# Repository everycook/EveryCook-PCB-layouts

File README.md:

EveryCook-PCB-layouts
=====================

All PCB layouts for the latest EveryCook. They work together, therefore they have a common repository

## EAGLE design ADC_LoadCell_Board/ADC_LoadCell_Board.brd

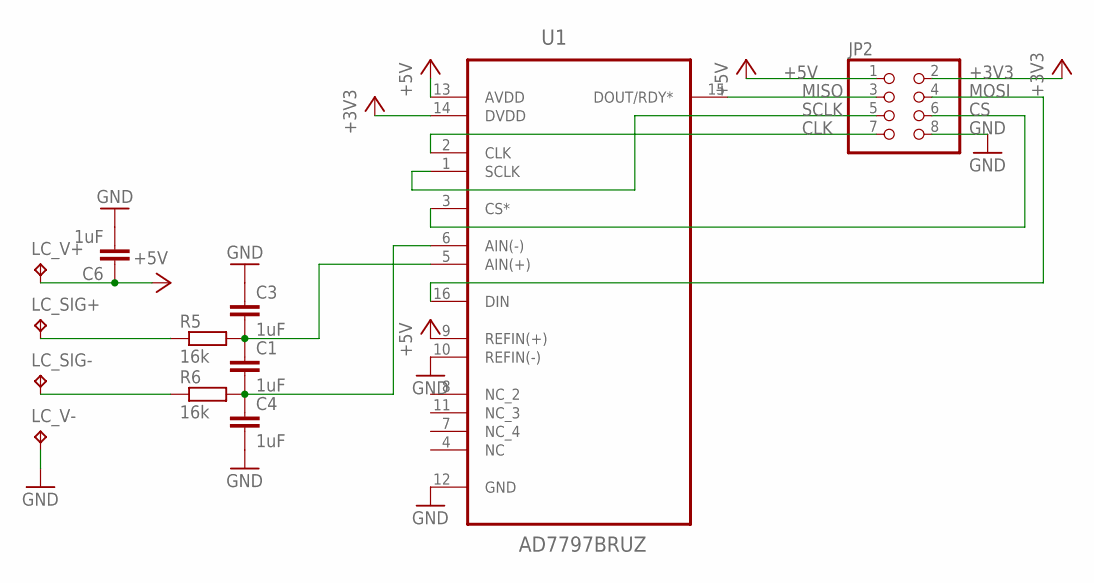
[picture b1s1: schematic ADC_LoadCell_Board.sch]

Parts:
C1, C3, C4, C6: 1uF; C0805
JP2: PINHD-2X4; 2X04
LC_SIG+: TPB1,27; B1,27
LC_SIG-: TPB1,27; B1,27
LC_V+: TPB1,27; B1,27
LC_V-: TPB1,27; B1,27
R5, R6: 16k; R0805
U1: AD7797BRUZ; SOP65P640X120-16N

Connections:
+3V3: JP2.2, U1.14 (DVDD)
+5V: C6.1, JP2.1, LC_V+.TP, U1.9 (REFIN(+)), U1.13 (AVDD)
CLK: JP2.7, U1.2 (CLK)
CS: JP2.6, U1.3 (CS*)
GND: C3.1, C4.2, C6.2, JP2.8, LC_V-.TP, U1.10 (REFIN(-)), U1.12 (GND)
MISO: JP2.3, U1.15 (DOUT/RDY*)
MOSI: JP2.4, U1.16 (DIN)
unnamed: LC_SIG+.TP, R5.1
unnamed: LC_SIG-.TP, R6.1
unnamed: C1.1, C3.2, R5.2, U1.5 (AIN(+))
unnamed: C1.2, C4.1, R6.2, U1.6 (AIN(-))
SCLK: JP2.5, U1.1 (SCLK)

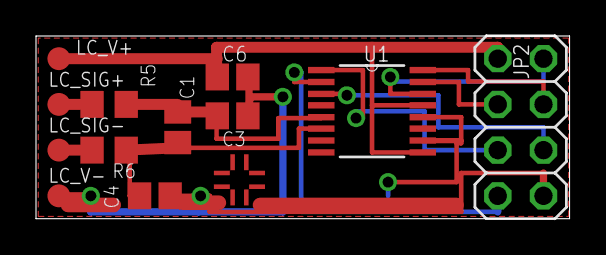
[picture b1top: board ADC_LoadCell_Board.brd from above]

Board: 2 copper layers, 29.6 x 10.2 mm, 13 parts (0 on the bottom side), 12 nets.

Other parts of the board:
U$2: PASSER

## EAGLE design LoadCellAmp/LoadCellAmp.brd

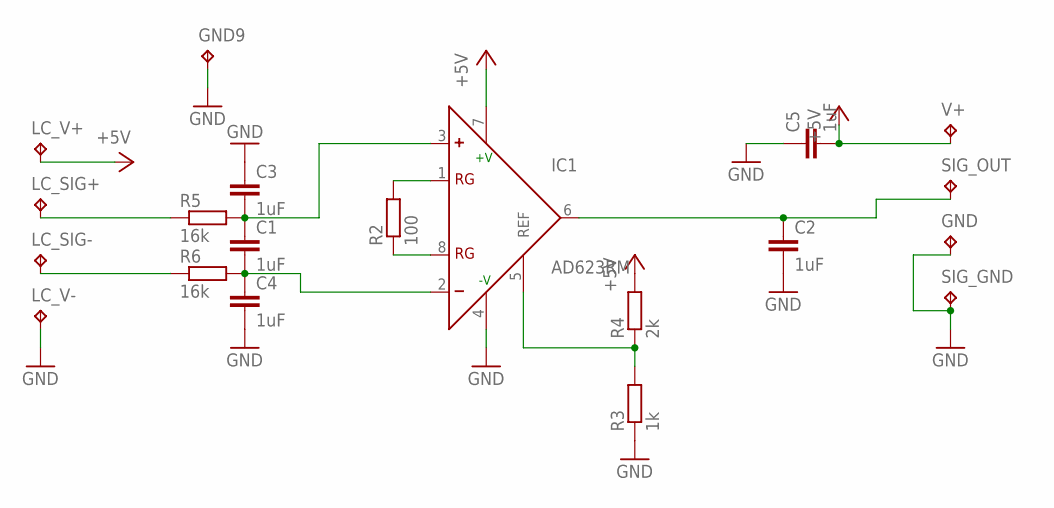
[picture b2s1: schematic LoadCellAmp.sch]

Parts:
C1, C2, C3, C4, C5: 1uF; C0805
GND, GND9: TPB1,27; B1,27
IC1: AD623RM; MSOP08
LC_SIG+: TPB1,27; B1,27
LC_SIG-: TPB1,27; B1,27
LC_V+: TPB1,27; B1,27
LC_V-: TPB1,27; B1,27
R2: 100; R0805
R3: 1k; R0805
R4: 2k; R0805
R5, R6: 16k; R0805
SIG_GND: TPB1,27; B1,27
SIG_OUT: TPB1,27; B1,27
V+: TPB1,27; B1,27

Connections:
+5V: C5.2, IC1.7 (+V), LC_V+.TP, R4.2, V+.TP
GND: C2.2, C3.1, C4.2, C5.1, GND.TP, GND9.TP, IC1.4 (-V), LC_V-.TP, R3.1, SIG_GND.TP
unnamed: IC1.1 (RG), R2.2
unnamed: IC1.8 (RG), R2.1
unnamed: IC1.5 (REF), R3.2, R4.1
unnamed: C2.1, IC1.6 (OUT), SIG_OUT.TP
unnamed: LC_SIG+.TP, R5.1
unnamed: LC_SIG-.TP, R6.1
unnamed: C1.1, C3.2, IC1.3 (+), R5.2
unnamed: C1.2, C4.1, IC1.2 (-), R6.2

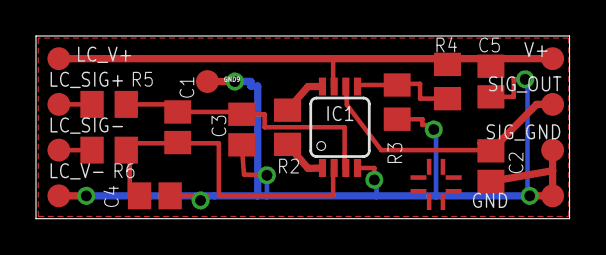
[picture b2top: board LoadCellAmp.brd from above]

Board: 2 copper layers, 29.6 x 10.2 mm, 21 parts (0 on the bottom side), 10 nets.

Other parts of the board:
U$2: PASSER

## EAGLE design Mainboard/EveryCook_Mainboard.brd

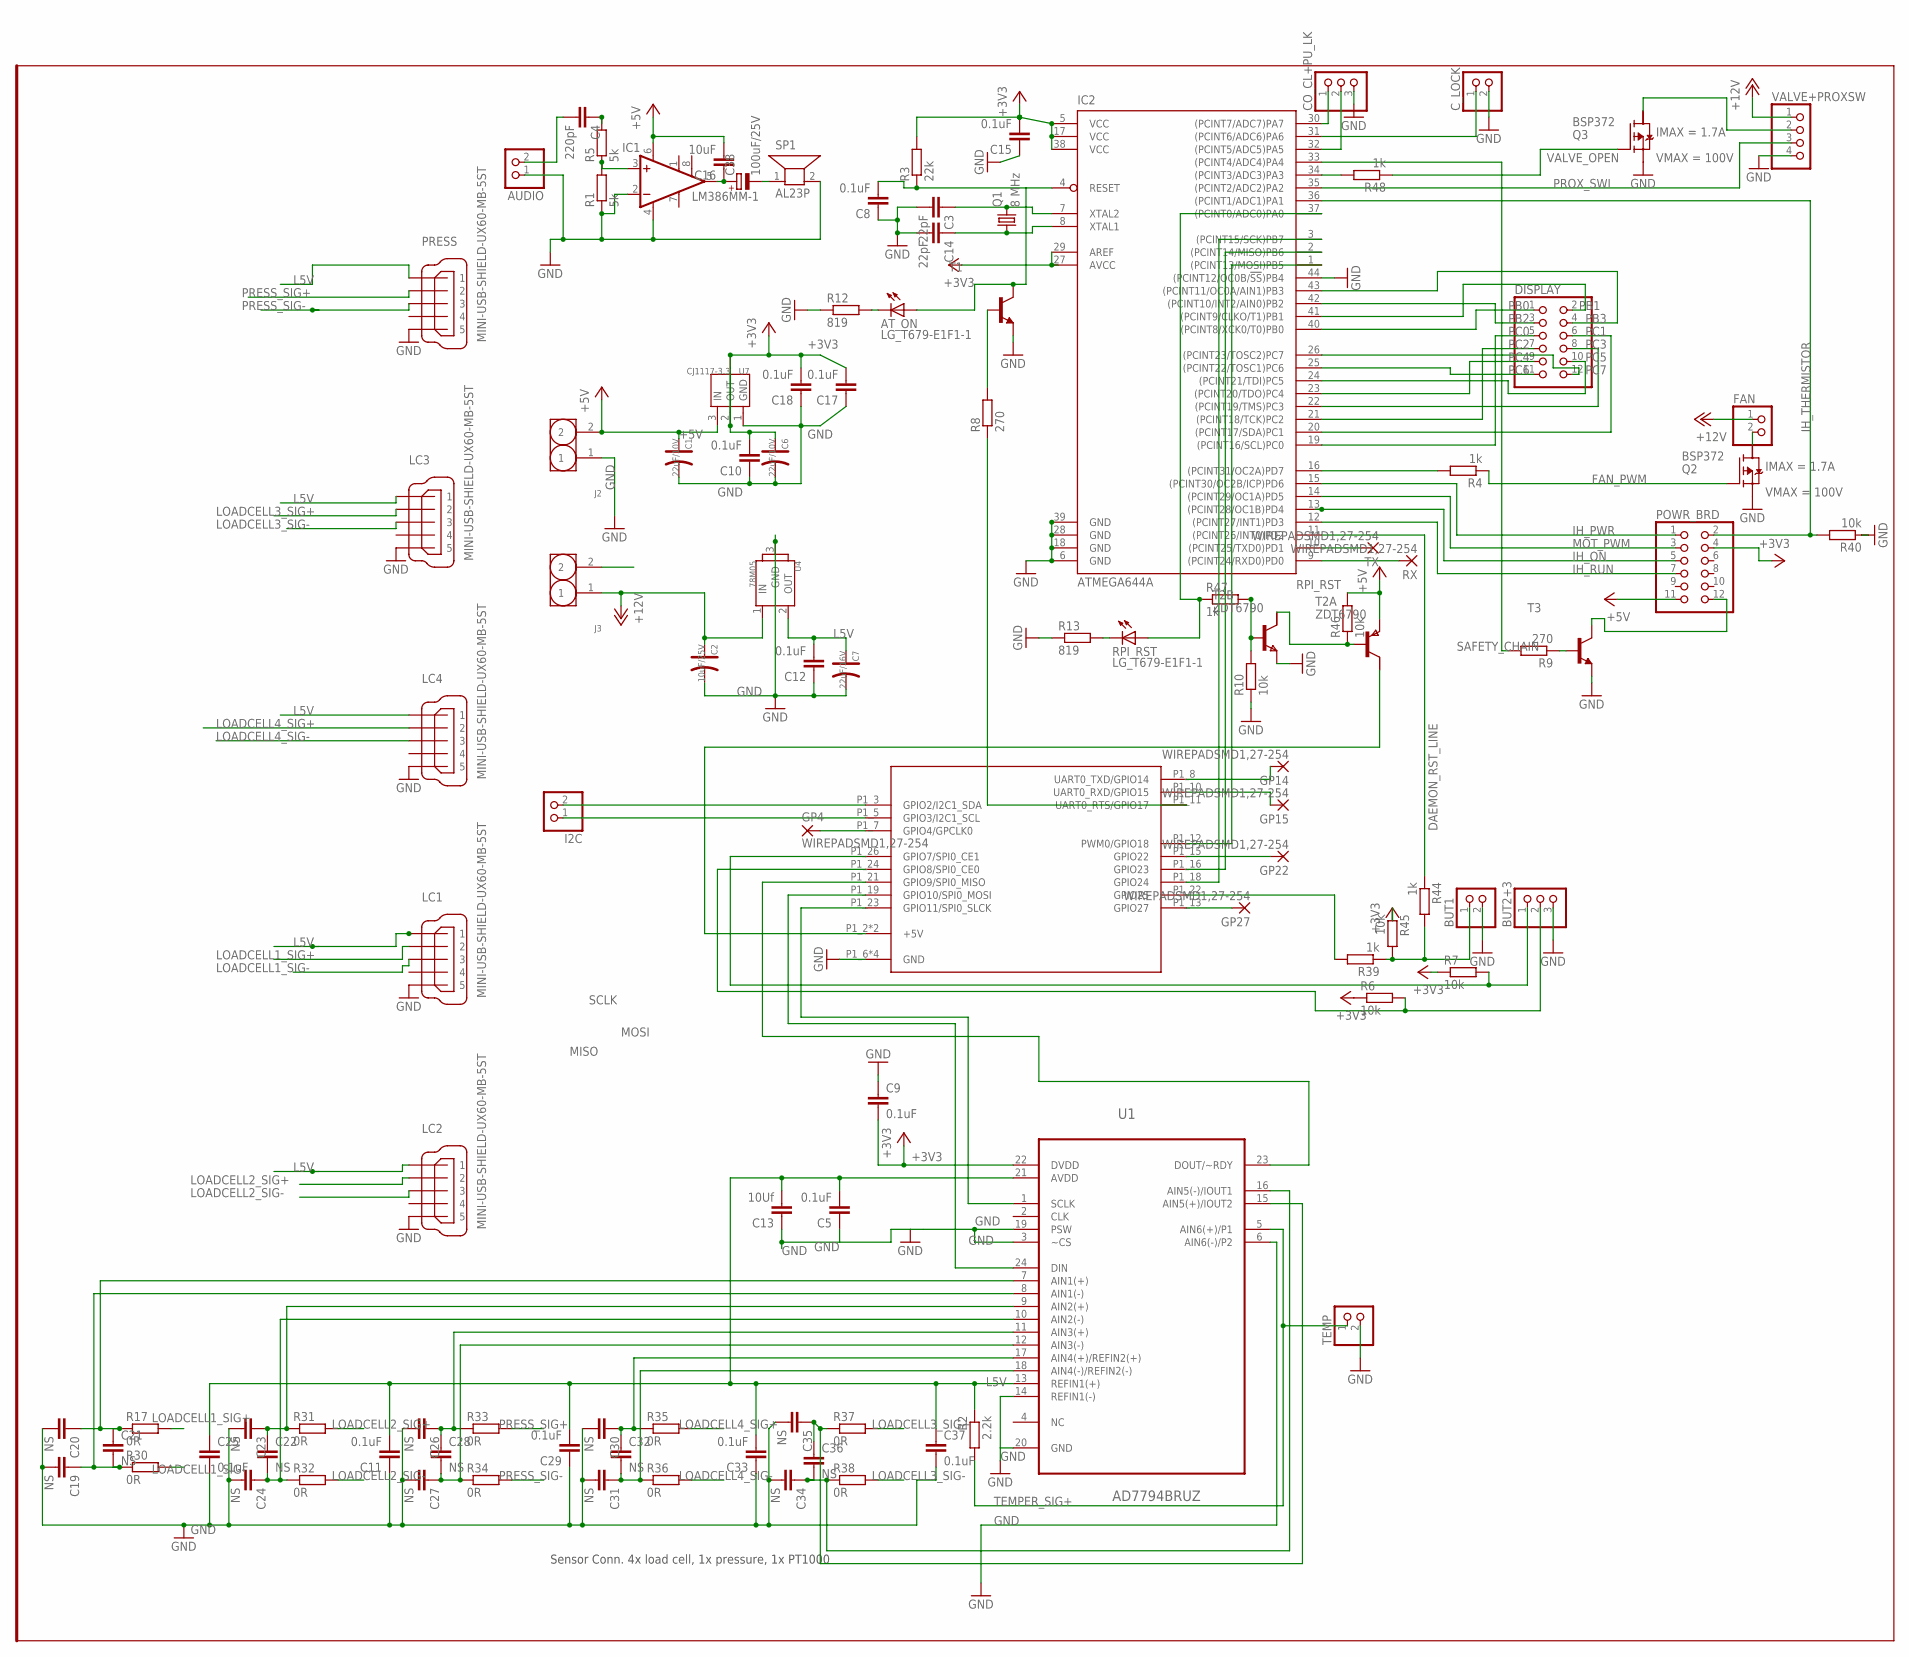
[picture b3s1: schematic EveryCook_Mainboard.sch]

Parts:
AT_ON: LG_T679-E1F1-1; PLCC2
AUDIO: PINHD-1X2; 1X02
BUT1: PINHD-1X2; 1X02
BUT2+3: PINHD-1X3; 1X03
C1, C6: 22uF/10V; AVX-A
C2: 10uF/25V; ELECTRO-SMD-B-4.8MM
C3, C14: 22pF; C0805
C4: 220pF; C0805
C5, C8, C9, C10, C11, C12, C15, C17, C18, C25, C29, C33, C37: 0.1uF; C0805
C7: 22uF/16V; ELECTRO-SMD-B-4.8MM
C13: 10Uf; C0805
C16: 10uF; C0805
C19, C20, C21, C22, C23, C24, C26, C27, C28, C30, C31, C32, C34, C35, C36: NS; C0805
C38: 100uF/25V; UD-6,3X7,7_NICHICON
CO_CL+PU_LK: PINHD-1X3; 1X03
C_LOCK: PINHD-1X2; 1X02
DISPLAY: PINHD-2X6; 2X06
FAN: PINHD-1X2; 1X02
GP4, GP14, GP15, GP22, GP27: WIREPADSMD1,27-254; SMD1,27-2,54
I2C: PINHD-1X2; 1X02
IC1: LM386MM-1; MMSOP08
IC2: ATMEGA644A; TQFP44
J2, J3: HEADER-2P-5.0; 2P-5.0
LC1, LC2, LC3, LC4: MINI-USB-SHIELD-UX60-MB-5ST; UX60-MB-5ST
POWR_BRD: PINHD-2X6; 2X06
PRESS: MINI-USB-SHIELD-UX60-MB-5ST; UX60-MB-5ST
Q1: 8 MHz; HC49UP
Q2, Q3: BSP372; PG-SOT-223
R1, R5: 5k; R0805
R2: 2.2k; R0805
R3: 22k; R0805
R4, R39, R44, R47, R48: 1k; R0805
R6, R7, R10, R40, R45, R46: 10k; R0805
R8, R9: 270; R0805
R12, R13: 819; R0805
R17, R30, R31, R32, R33, R34, R35, R36, R37, R38: 0R; R0805
RPI_RST: LG_T679-E1F1-1; PLCC2
RX: WIREPADSMD1,27-254; SMD1,27-2,54
SP1: AL23P
T1, T3: MMBT2222ALT1-NPN-SOT23-BEC; SOT23-BEC
T2: ZDT6790; SM8
TEMP: PINHD-1X2; 1X02
TX: WIREPADSMD1,27-254; SMD1,27-2,54
U1: AD7794BRUZ; SOP65P640X120-24N
U4: 78M05; TO252
U7: CJ1117-3.3; SOT89
U$5: RPI-B-V2
VALVE+PROXSW: PINHD-1X4; 1X04

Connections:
+3V3: C6.+, C9.2, C10.2, C15.2, C17.2, C18.2, IC2.5 (VCC), IC2.17 (VCC), IC2.27 (AVCC), IC2.29 (AREF), IC2.38 (VCC), POWR_BRD.4, R3.2, R6.1, R7.1, R45.1, U1.22 (DVDD), U7.2 (OUT), U7.4 (TAB)
+5V: C1.+, C16.2, IC1.6 (VS), J2.2, POWR_BRD.11, R46.2, T2.1 (E), U7.3 (IN)
+12V: C2.+, FAN.1, J3.1, U4.1 (IN), VALVE+PROXSW.1
ATMEL_RST: AT_ON.A, C8.2, IC2.4 (RESET), R3.1, T1.C
AT_MISO: IC2.2 ((PCINT14/MISO)PB6), U$5.P1_16 (GPIO23)
AT_MOSI: IC2.1 ((PCINT13/MOSI)PB5), U$5.P1_12 (PWM0/GPIO18)
C_CLOSE: CO_CL+PU_LK.1, IC2.30 ((PCINT7/ADC7)PA7)
DAEMON_RST_LINE: IC2.11 ((PCINT26/INT0)PD2), R44.1
FAN_PWM: Q2.1 (G), R4.1
GND: AUDIO.1, BUT1.2, BUT2+3.3, C1.-, C2.-, C3.2, C5.1, C6.-, C7.-, C8.1, C9.1, C10.1, C11.1, C12.1, C13.1, C14.2, C15.1, C17.1, C18.1, C19.2, C20.2, C23.2, C24.2, C25.2, C26.2, C27.2, C29.1, C30.2, C31.2, C33.1, C34.2, C35.2, C37.2, CO_CL+PU_LK.3, C_LOCK.2, IC1.2 (-IN), IC1.4 (GND), IC2.6 (GND), IC2.18 (GND), IC2.28 (GND), IC2.39 (GND), IC2.44 ((PCINT12/OC0B/!SS!)PB4), J2.1, LC1.5, LC2.5, LC3.5, LC4.5, PRESS.5, Q2.3 (S), Q3.3 (S), R1.1, R10.1, R12.1, R13.1, R40.1, SP1.2, T1.E, T2.3 (E), T3.E, TEMP.2, U1.3 (~CS), U1.6 (AIN6(-)/P2), U1.14 (REFIN1(-)), U1.19 (PSW), U1.20 (GND), U4.3 (GND), U7.1 (GND), U$5.P1_6 (GND), U$5.P1_14 (GND), U$5.P1_20 (GND), U$5.P1_25 (GND), VALVE+PROXSW.4
IH_ON: IC2.13 ((PCINT28/OC1B)PD4), POWR_BRD.5
IH_PWR: IC2.15 ((PCINT30/OC2B/ICP)PD6), POWR_BRD.1
IH_RUN: IC2.12 ((PCINT27/INT1)PD3), POWR_BRD.7
IH_THERMISTOR: IC2.36 ((PCINT1/ADC1)PA1), POWR_BRD.2, R40.2
L5V: C5.2, C7.+, C11.2, C12.2, C13.2, C25.1, C29.2, C33.2, C37.1, LC1.1, LC2.1, LC3.1, LC4.1, PRESS.1, R2.1, U1.13 (REFIN1(+)), U1.21 (AVDD), U4.2 (OUT)
LOADCELL1_SIG+: LC1.2, R17.2
LOADCELL1_SIG-: LC1.3, R30.2
LOADCELL2_SIG+: LC2.2, R31.2
LOADCELL2_SIG-: LC2.3, R32.2
LOADCELL3_SIG+: LC3.2, R37.2
LOADCELL3_SIG-: LC3.3, R38.2
LOADCELL4_SIG+: LC4.2, R35.2
LOADCELL4_SIG-: LC4.3, R36.2
MISO: U1.23 (DOUT/~RDY), U$5.P1_21 (GPIO9/SPI0_MISO)
MOSI: U1.24 (DIN), U$5.P1_19 (GPIO10/SPI0_MOSI)
MOT_PWM: IC2.14 ((PCINT29/OC1A)PD5), POWR_BRD.3
unnamed: I2C.1, U$5.P1_5 (GPIO3/I2C1_SCL)
unnamed: C3.1, IC2.7 (XTAL2), Q1.2
unnamed: C4.1, R5.2
unnamed: C34.1, C36.2, R38.1, U1.16 (AIN5(-)/IOUT1)
unnamed: I2C.2, U$5.P1_3 (GPIO2/I2C1_SDA)
unnamed: C14.1, IC2.8 (XTAL1), Q1.1
unnamed: POWR_BRD.12, T3.C
unnamed: C20.1, C21.1, R17.1, U1.7 (AIN1(+))
unnamed: IC2.16 ((PCINT31/OC2A)PD7), R4.2
unnamed: R9.1, T3.B
unnamed: IC2.10 ((PCINT25/TXD0)PD1), TX.1
unnamed: IC1.3 (+IN), R1.2, R5.1
unnamed: IC2.9 ((PCINT24/RXD0)PD0), RX.1
unnamed: GP4.1, U$5.P1_7 (GPIO4/GPCLK0)
unnamed: GP27.1, U$5.P1_13 (GPIO27)
unnamed: GP22.1, U$5.P1_15 (GPIO22)
unnamed: GP15.1, U$5.P1_10 (UART0_RXD/GPIO15)
unnamed: GP14.1, U$5.P1_8 (UART0_TXD/GPIO14)
unnamed: C16.1, C38.+, IC1.5 (OUT)
unnamed: C38.-, SP1.1
unnamed: C22.1, C23.1, R31.1, U1.9 (AIN2(+))
unnamed: R8.2, T1.B
unnamed: AUDIO.2, C4.2
unnamed: AT_ON.C, R12.2
unnamed: R13.2, RPI_RST.C
unnamed: C22.2, C24.1, R32.1, U1.10 (AIN2(-))
unnamed: C27.1, C28.2, R34.1, U1.12 (AIN3(-))
unnamed: C30.1, C32.1, R35.1, U1.17 (AIN4(+)/REFIN2(+))
unnamed: C31.1, C32.2, R36.1, U1.18 (AIN4(-)/REFIN2(-))
unnamed: C35.1, C36.1, R37.1, U1.15 (AIN5(+)/IOUT2)
unnamed: C19.1, C21.2, R30.1, U1.8 (AIN1(-))
unnamed: FAN.2, Q2.2 (D)
unnamed: C26.1, C28.1, R33.1, U1.11 (AIN3(+))
unnamed: T2.8 (C1), U$5.P1_2 (+5V), U$5.P1_4 (+5V)
unnamed: C_LOCK.1, IC2.31 ((PCINT6/ADC6)PA6)
unnamed: BUT2+3.1, R7.2, U$5.P1_26 (GPIO7/SPI0_CE1)
unnamed: BUT2+3.2, R6.2, U$5.P1_24 (GPIO8/SPI0_CE0)
unnamed: R39.2, U$5.P1_22 (GPIO25)
unnamed: IC2.34 ((PCINT3/ADC3)PA3), R48.2
unnamed: BUT1.1, R39.1, R44.2, R45.2
unnamed: R10.2, R47.2, T2.4 (B)
unnamed: R46.1, T2.2 (B), T2.5 (C1)
unnamed: Q3.2 (D), VALVE+PROXSW.2
PB0: DISPLAY.1, IC2.40 ((PCINT8/XCK0/T0)PB0)
PB1: DISPLAY.2, IC2.41 ((PCINT9/CLKO/T1)PB1)
PB2: DISPLAY.3, IC2.42 ((PCINT10/INT2/AIN0)PB2)
PB3: DISPLAY.4, IC2.43 ((PCINT11/OC0A/AIN1)PB3)
PC0: DISPLAY.5, IC2.19 ((PCINT16/SCL)PC0)
PC1: DISPLAY.6, IC2.20 ((PCINT17/SDA)PC1)
PC2: DISPLAY.7, IC2.21 ((PCINT18/TCK)PC2)
PC3: DISPLAY.8, IC2.22 ((PCINT19/TMS)PC3)
PC4: DISPLAY.9, IC2.23 ((PCINT20/TDO)PC4)
PC5: DISPLAY.10, IC2.24 ((PCINT21/TDI)PC5)
PC6: DISPLAY.11, IC2.25 ((PCINT22/TOSC1)PC6)
PC7: DISPLAY.12, IC2.26 ((PCINT23/TOSC2)PC7)
PGND: J3.2
PRESS_SIG+: PRESS.2, R33.2
PRESS_SIG-: PRESS.3, R34.2
PROX_SWI: IC2.35 ((PCINT2/ADC2)PA2), VALVE+PROXSW.3
P_LOCK: CO_CL+PU_LK.2, IC2.32 ((PCINT5/ADC5)PA5)
RPI_ATMEL_RST: R8.1, U$5.P1_11 (UART0_RTS/GPIO17)
RPI_RST: IC2.37 ((PCINT0/ADC0)PA0), R47.1, RPI_RST.A
SAFETY_CHAIN: IC2.33 ((PCINT4/ADC4)PA4), R9.2
SCK: IC2.3 ((PCINT15/SCK)PB7), U$5.P1_18 (GPIO24)
SCLK: U1.1 (SCLK), U$5.P1_23 (GPIO11/SPI0_SLCK)
TEMPER_SIG+: R2.2, TEMP.1, U1.5 (AIN6(+)/P1)
VALVE_OPEN: Q3.1 (G), R48.1

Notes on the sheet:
Sensor Conn. 4x load cell, 1x pressure, 1x PT1000

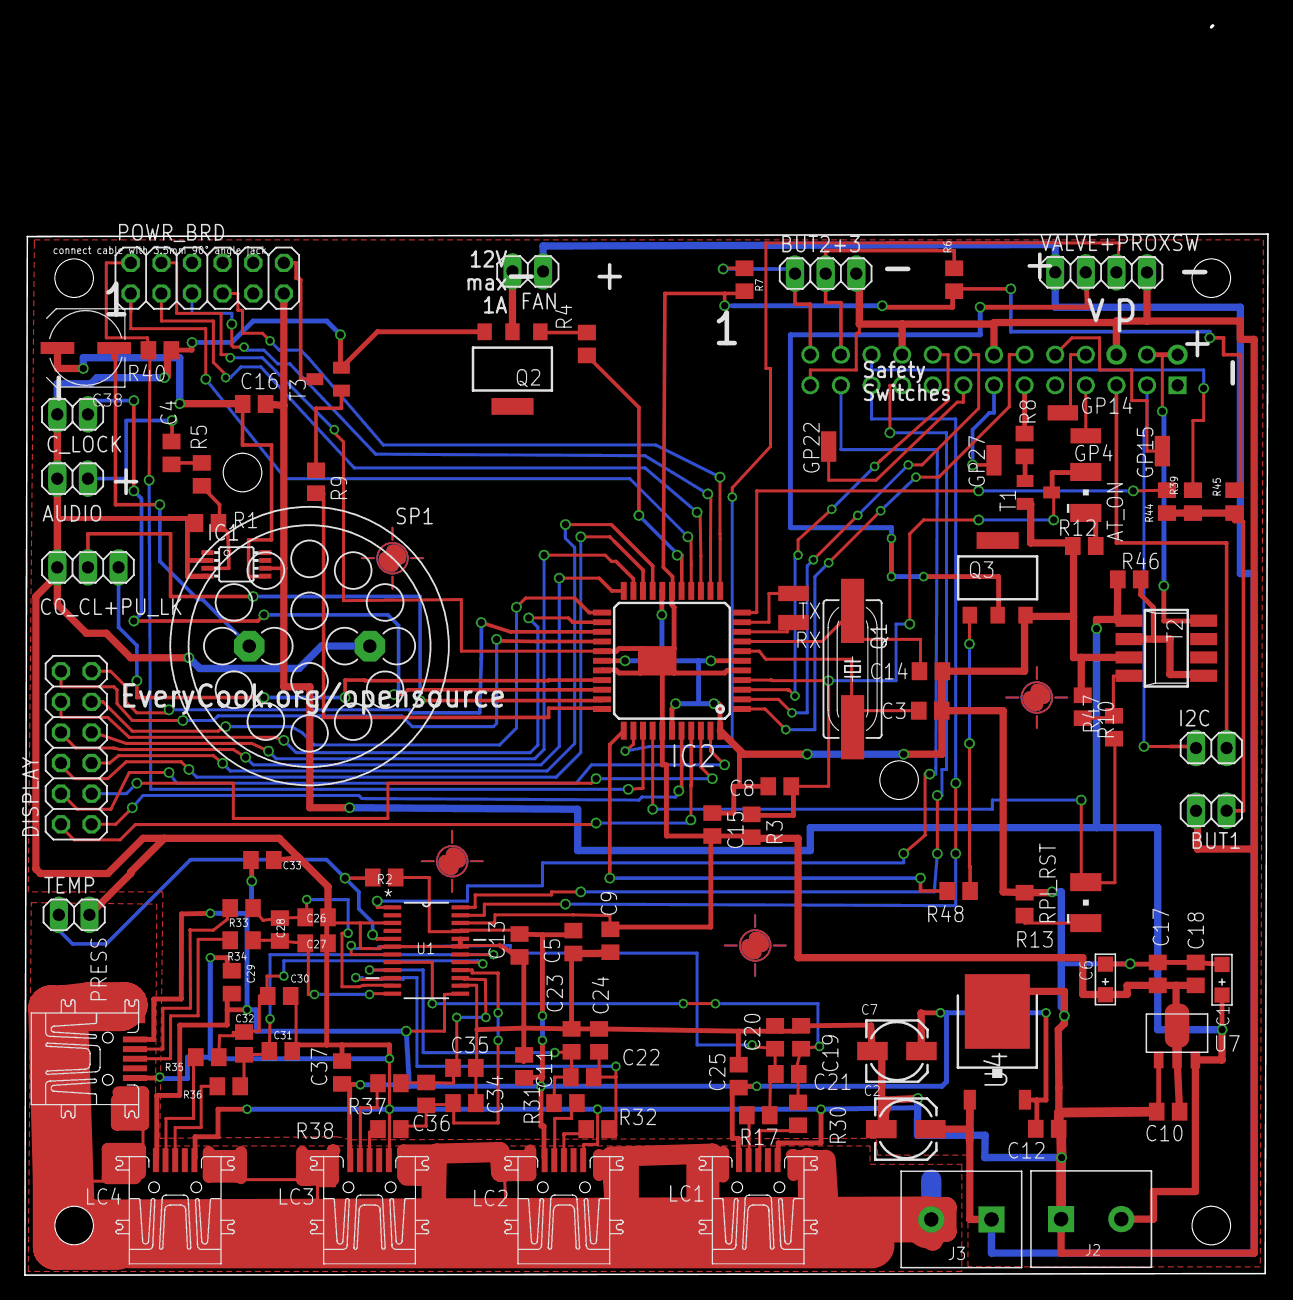
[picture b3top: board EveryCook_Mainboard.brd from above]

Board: 2 copper layers, 103.1 x 86.4 mm, 111 parts (0 on the bottom side), 92 nets.

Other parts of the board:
U$1, U$2, U$3, U$4: PASS-ROUND

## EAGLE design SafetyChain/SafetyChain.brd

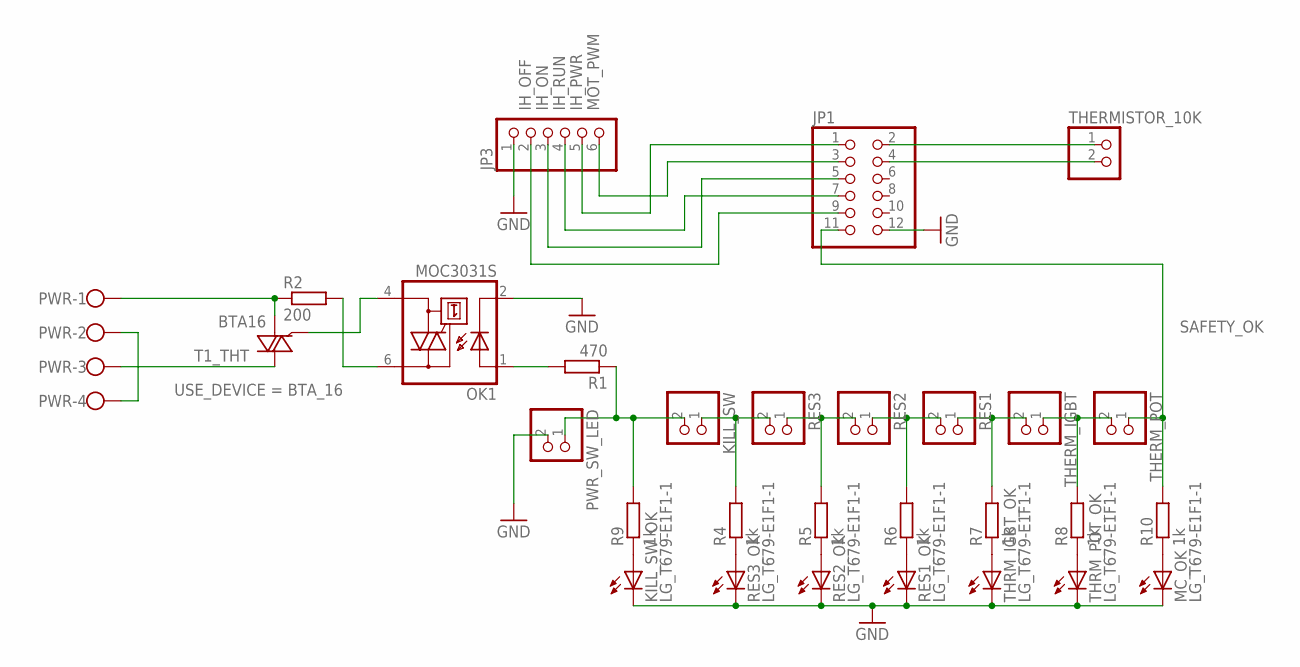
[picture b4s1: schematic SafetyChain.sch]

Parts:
JP1: PINHD-2X6; 2X06
JP3: PINHD-1X6; 1X06
KILL_SW: PINHD-1X2; 1X02
KILL_SW_OK: LG_T679-E1F1-1; PLCC2
MC_OK: LG_T679-E1F1-1; PLCC2
OK1: MOC3031S; DIL6-SMD
PWR: W237-4
PWR_SW_LED: PINHD-1X2; 1X02
R1: 470; M0805
R2: 200; M0805
R4, R5, R6, R7, R8, R9, R10: 1k; M0805
RES1, RES2, RES3: PINHD-1X2; 1X02
RES1_OK, RES2_OK, RES3_OK: LG_T679-E1F1-1; PLCC2
T1_THT: BTA16; TO220BV
THERMISTOR_10K: PINHD-1X2; 1X02
THERM_IGBT: PINHD-1X2; 1X02
THERM_POT: PINHD-1X2; 1X02
THRM_IGBT_OK: LG_T679-E1F1-1; PLCC2
THRM_POT_OK: LG_T679-E1F1-1; PLCC2

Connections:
3V3: JP1.4, THERMISTOR_10K.2
GND: JP1.12, JP3.1, KILL_SW_OK.C, MC_OK.C, OK1.2 (C), PWR_SW_LED.2, RES1_OK.C, RES2_OK.C, RES3_OK.C, THRM_IGBT_OK.C, THRM_POT_OK.C
IH_OFF: JP1.9, JP3.2
IH_ON: JP1.5, JP3.3
IH_PWR: JP1.1, JP3.5
IH_RUN: JP1.7, JP3.4
IH_THERMISTOR: JP1.2, THERMISTOR_10K.1
L_IN: PWR.1, R2.1, T1_THT.T1 (A1)
L_OUT: PWR.3, T1_THT.T2 (A2)
MOT_PWM: JP1.3, JP3.6
unnamed: OK1.1 (A), R1.2
unnamed: OK1.6 (A2), R2.2
unnamed: R8.2, THERM_IGBT.1, THERM_POT.2
unnamed: R7.2, RES1.1, THERM_IGBT.2
unnamed: R6.2, RES1.2, RES2.1
unnamed: R5.2, RES2.2, RES3.1
unnamed: KILL_SW.1, R4.2, RES3.2
unnamed: KILL_SW.2, PWR_SW_LED.1, R1.1, R9.2
unnamed: R4.1, RES3_OK.A
unnamed: R5.1, RES2_OK.A
unnamed: R6.1, RES1_OK.A
unnamed: R7.1, THRM_IGBT_OK.A
unnamed: R8.1, THRM_POT_OK.A
unnamed: MC_OK.A, R10.1
unnamed: KILL_SW_OK.A, R9.1
PWR_N: PWR.2, PWR.4
SAFETY_OK: JP1.11, R10.2, THERM_POT.1
TRIAC_DRV: OK1.4 (A1), T1_THT.G

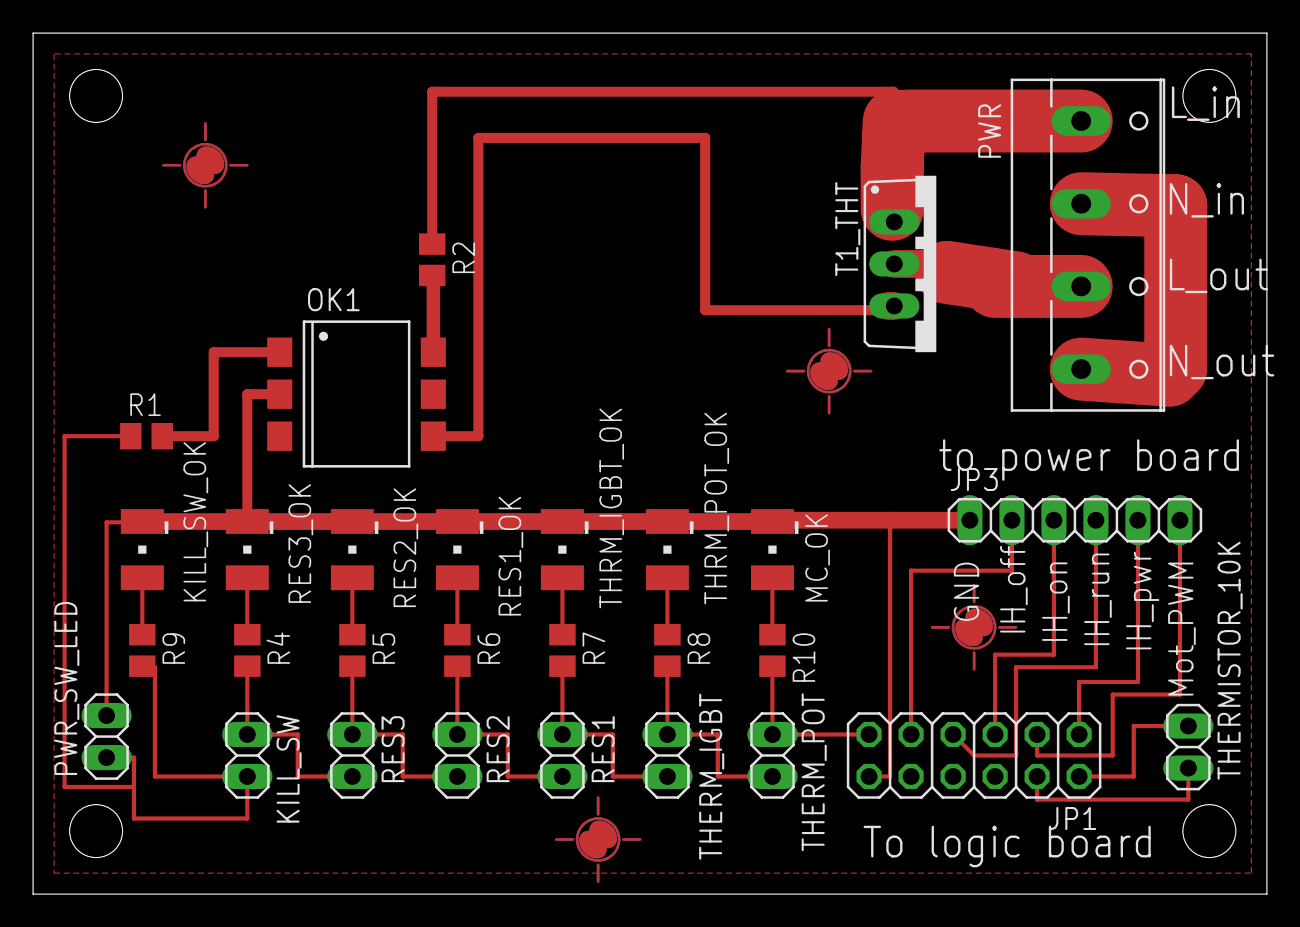
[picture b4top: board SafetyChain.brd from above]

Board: 2 copper layers, 74.6 x 52.1 mm, 33 parts (0 on the bottom side), 28 nets.

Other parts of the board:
U$1, U$2, U$3, U$4: PASS-ROUND

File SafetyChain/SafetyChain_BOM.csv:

Part	Value	Device	Package	Description	COLOR	MF	MPN	OC_FARNELL	OC_NEWARK	USE_DEVICE
JP1		PINHD-2X6	2X06	PIN HEADER						
JP3		PINHD-1X6	1X06	PIN HEADER						
KILL_SW		PINHD-1X2	1X02	PIN HEADER						
KILL_SW_OK	LG_T679-E1F1-1	LG_T679-E1F1-1	PLCC2	LC TOPLED® Low Current LED	green					
MC_OK	LG_T679-E1F1-1	LG_T679-E1F1-1	PLCC2	LC TOPLED® Low Current LED	green					
OK1	MOC3031S	MOC3031S	DIL6-SMD	6-Pin DIP Zero-Cross Optoisolators Triac Driver Output (250/400 Volt Peak)		FAIRCHILD SEMICONDUCTOR	MOC3031SM	unknown	34C1335	
PWR		W237-4	W237-4	WAGO SCREW CLAMP				unknown	unknown	
PWR_SW_LED		PINHD-1X2	1X02	PIN HEADER						
R1	470	R-EU_M0805	M0805	RESISTOR, European symbol						
R2	200	R-EU_M0805	M0805	RESISTOR, European symbol						
R4	1k	R-EU_M0805	M0805	RESISTOR, European symbol						
R5	1k	R-EU_M0805	M0805	RESISTOR, European symbol						
R6	1k	R-EU_M0805	M0805	RESISTOR, European symbol						
R7	1k	R-EU_M0805	M0805	RESISTOR, European symbol						
R8	1k	R-EU_M0805	M0805	RESISTOR, European symbol						
R9	1k	R-EU_M0805	M0805	RESISTOR, European symbol						
R10	1k	R-EU_M0805	M0805	RESISTOR, European symbol						
RES1		PINHD-1X2	1X02	PIN HEADER						
RES1_OK	LG_T679-E1F1-1	LG_T679-E1F1-1	PLCC2	LC TOPLED® Low Current LED	green					
RES2		PINHD-1X2	1X02	PIN HEADER						
RES2_OK	LG_T679-E1F1-1	LG_T679-E1F1-1	PLCC2	LC TOPLED® Low Current LED	green					
RES3		PINHD-1X2	1X02	PIN HEADER						
RES3_OK	LG_T679-E1F1-1	LG_T679-E1F1-1	PLCC2	LC TOPLED® Low Current LED	green					
T1_THT	BTA16	BTA17	TO220BV	THT						BTA_16
THERMISTOR_10K		PINHD-1X2	1X02	PIN HEADER						
THERM_IGBT		PINHD-1X2	1X02	PIN HEADER						
THERM_POT		PINHD-1X2	1X02	PIN HEADER						
THRM_IGBT_OK	LG_T679-E1F1-1	LG_T679-E1F1-1	PLCC2	LC TOPLED® Low Current LED	green					
THRM_POT_OK	LG_T679-E1F1-1	LG_T679-E1F1-1	PLCC2	LC TOPLED® Low Current LED	green

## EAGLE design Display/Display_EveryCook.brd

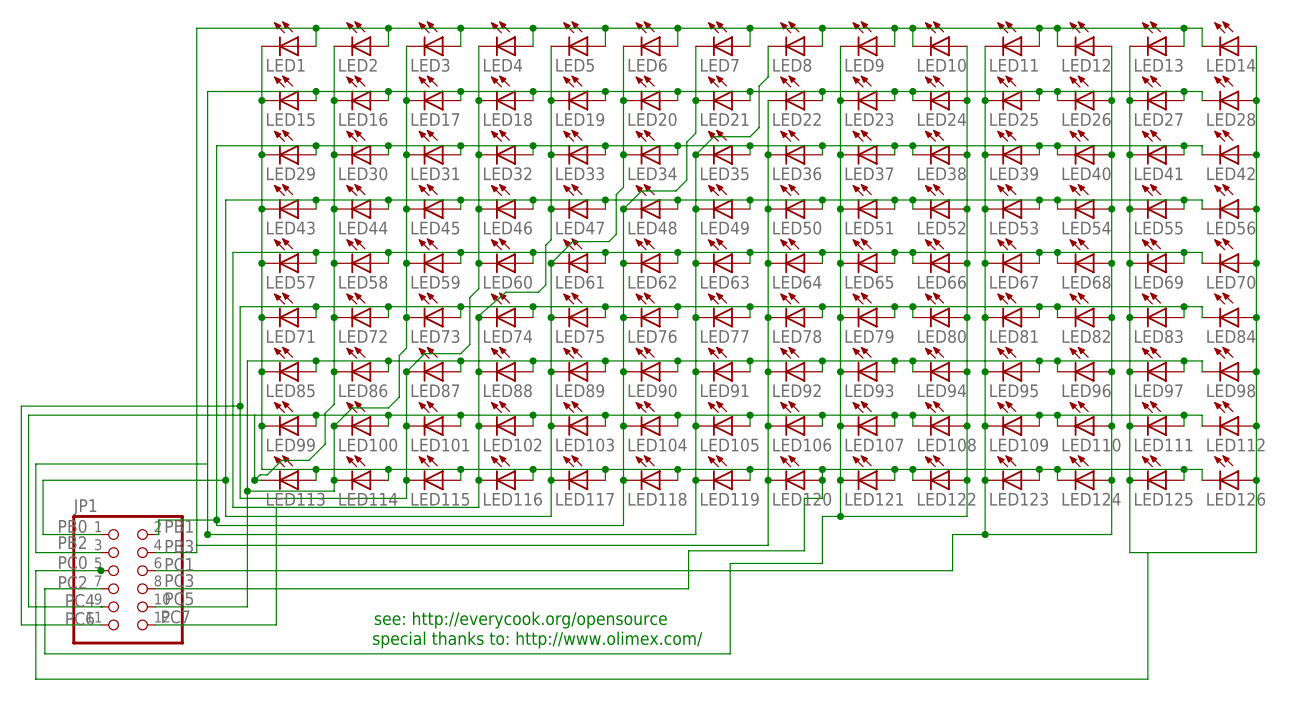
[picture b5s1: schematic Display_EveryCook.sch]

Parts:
JP1: PINHD-2X6; 2X06
LED1, LED2, LED3, LED4, LED5, LED6, LED7, LED8, LED9, LED10, LED11, LED12, LED13, LED14, LED15, LED16, LED17, LED18, LED19, LED20, LED21, LED22, LED23, LED24, LED25, LED26, LED27, LED28, LED29, LED30, LED31, LED32, LED33, LED34, LED35, LED36, LED37, LED38, LED39, LED40, LED41, LED42, LED43, LED44, LED45, LED46, LED47, LED48, LED49, LED50, LED51, LED52, LED53, LED54, LED55, LED56, LED57, LED58, LED59, LED60, LED61, LED62, LED63, LED64, LED65, LED66, LED67, LED68, LED69, LED70, LED71, LED72, LED73, LED74, LED75, LED76, LED77, LED78, LED79, LED80, LED81, LED82, LED83, LED84, LED85, LED86, LED87, LED88, LED89, LED90, LED91, LED92, LED93, LED94, LED95, LED96, LED97, LED98, LED99, LED100, LED101, LED102, LED103, LED104, LED105, LED106, LED107, LED108, LED109, LED110, LED111, LED112, LED113, LED114, LED115, LED116, LED117, LED118, LED119, LED120, LED121, LED122, LED123, LED124, LED125, LED126: LEDKA-3528ASYC; KA-3528ASYC

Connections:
PB0: JP1.1, LED6.C, LED20.C, LED34.C, LED43.A, LED44.A, LED45.A, LED46.A, LED47.A, LED48.A, LED49.A, LED50.A, LED51.A, LED52.C, LED53.A, LED54.C, LED55.A, LED56.C, LED61.C, LED75.C, LED89.C, LED103.C, LED117.C
PB1: JP1.2, LED7.C, LED21.C, LED29.A, LED30.A, LED31.A, LED32.A, LED33.A, LED34.A, LED35.A, LED36.A, LED37.A, LED38.C, LED39.A, LED40.C, LED41.A, LED42.C, LED48.C, LED62.C, LED76.C, LED90.C, LED104.C, LED118.C
PB2: JP1.3, LED8.C, LED15.A, LED16.A, LED17.A, LED18.A, LED19.A, LED20.A, LED21.A, LED22.A, LED23.A, LED24.C, LED25.A, LED26.C, LED27.A, LED28.C, LED35.C, LED49.C, LED63.C, LED77.C, LED91.C, LED105.C, LED119.C
PB3: JP1.4, LED1.A, LED2.A, LED3.A, LED4.A, LED5.A, LED6.A, LED7.A, LED8.A, LED9.A, LED10.C, LED11.A, LED12.C, LED13.A, LED14.C, LED22.C, LED36.C, LED50.C, LED64.C, LED78.C, LED92.C, LED106.C, LED120.C
PC0: JP1.5, LED13.C, LED14.A, LED27.C, LED28.A, LED41.C, LED42.A, LED55.C, LED56.A, LED69.C, LED70.A, LED83.C, LED84.A, LED97.C, LED98.A, LED111.C, LED112.A, LED125.C, LED126.A
PC1: JP1.6, LED11.C, LED12.A, LED25.C, LED26.A, LED39.C, LED40.A, LED53.C, LED54.A, LED67.C, LED68.A, LED81.C, LED82.A, LED95.C, LED96.A, LED109.C, LED110.A, LED123.C, LED124.A
PC2: JP1.7, LED9.C, LED10.A, LED23.C, LED24.A, LED37.C, LED38.A, LED51.C, LED52.A, LED65.C, LED66.A, LED79.C, LED80.A, LED93.C, LED94.A, LED107.C, LED108.A, LED121.C, LED122.A
PC3: JP1.8, LED1.C, LED15.C, LED29.C, LED43.C, LED57.C, LED71.C, LED85.C, LED99.C, LED113.A, LED114.A, LED115.A, LED116.A, LED117.A, LED118.A, LED119.A, LED120.A, LED121.A, LED122.C, LED123.A, LED124.C, LED125.A, LED126.C
PC4: JP1.9, LED2.C, LED16.C, LED30.C, LED44.C, LED58.C, LED72.C, LED86.C, LED99.A, LED100.A, LED101.A, LED102.A, LED103.A, LED104.A, LED105.A, LED106.A, LED107.A, LED108.C, LED109.A, LED110.C, LED111.A, LED112.C, LED113.C
PC5: JP1.10, LED3.C, LED17.C, LED31.C, LED45.C, LED59.C, LED73.C, LED85.A, LED86.A, LED87.A, LED88.A, LED89.A, LED90.A, LED91.A, LED92.A, LED93.A, LED94.C, LED95.A, LED96.C, LED97.A, LED98.C, LED100.C, LED114.C
PC6: JP1.11, LED4.C, LED18.C, LED32.C, LED46.C, LED60.C, LED71.A, LED72.A, LED73.A, LED74.A, LED75.A, LED76.A, LED77.A, LED78.A, LED79.A, LED80.C, LED81.A, LED82.C, LED83.A, LED84.C, LED87.C, LED101.C, LED115.C
PC7: JP1.12, LED5.C, LED19.C, LED33.C, LED47.C, LED57.A, LED58.A, LED59.A, LED60.A, LED61.A, LED62.A, LED63.A, LED64.A, LED65.A, LED66.C, LED67.A, LED68.C, LED69.A, LED70.C, LED74.C, LED88.C, LED102.C, LED116.C

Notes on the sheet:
special thanks to: http://www.olimex.com/
see: http://everycook.org/opensource

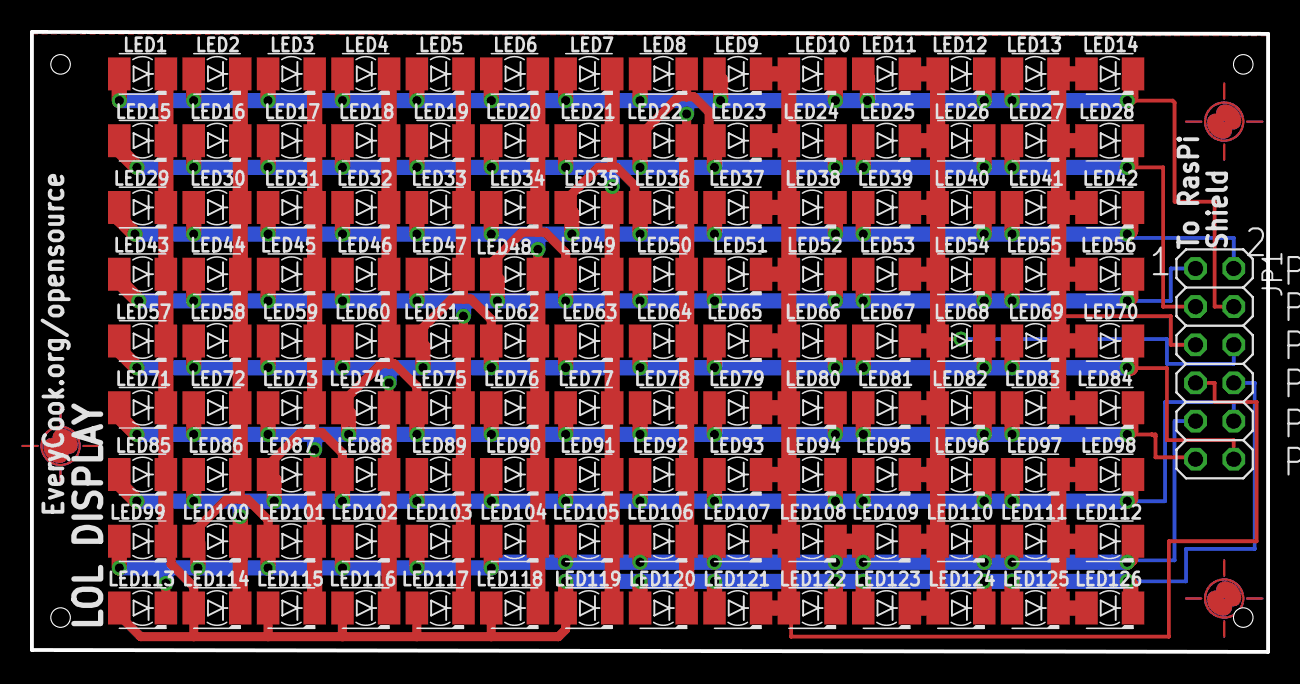
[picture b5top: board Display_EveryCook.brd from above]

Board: 2 copper layers, 82.3 x 41.3 mm, 130 parts (0 on the bottom side), 12 nets.

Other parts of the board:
U$1, U$2, U$3: PASS-ROUND

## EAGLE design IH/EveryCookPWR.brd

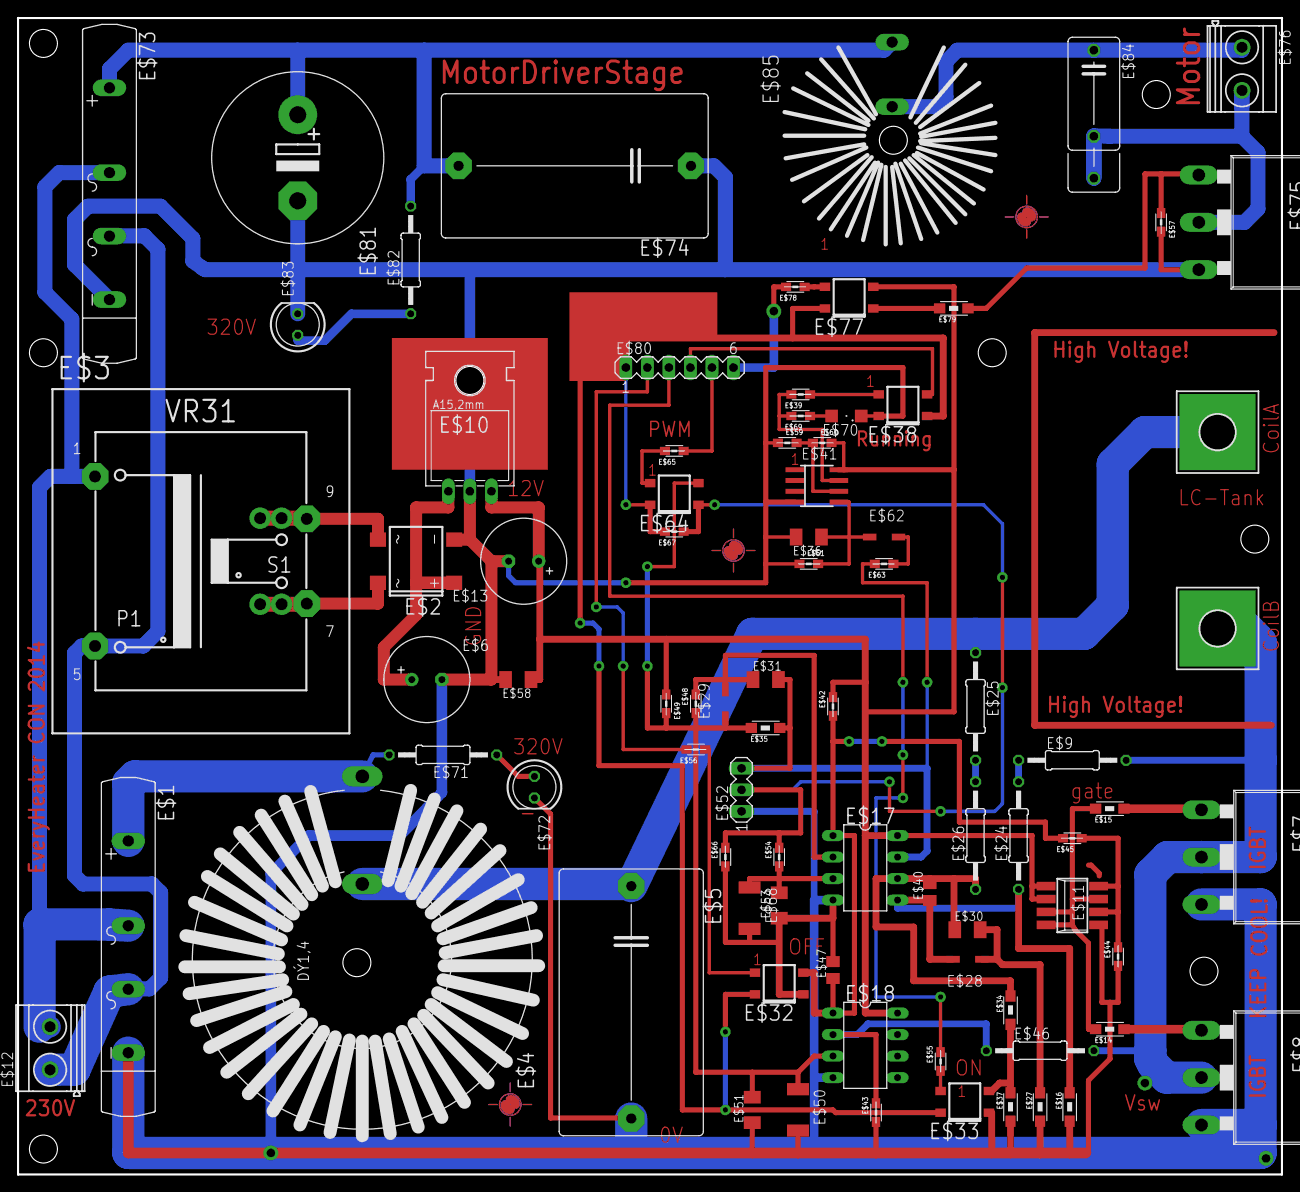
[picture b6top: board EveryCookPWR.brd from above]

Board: 2 copper layers, 149.2 x 136.5 mm, 85 parts (0 on the bottom side), 51 nets.

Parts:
E$1, E$73: GBI25M; SKB50
E$2: DBS
E$3: VR31
E$4: 330uH (SDO-40-5.00-330); ED43
E$5, E$74: 6.8uF (B32674D4685K000); C27.5B17
E$6, E$13: 220uF; E3,5-10
E$7, E$8, E$75: FGA25120N; TO247BH
E$9, E$24: 300k; 0207/12
E$10: 7812; 78XXL_S
E$11: ZDT6790; SM8
E$12, E$76: MKDSN1,5/2-5,08
E$14, E$15: 10; 1206
E$16: 6k8; 1206
E$17, E$18: LM2903N; DIL8
E$19, E$20: 4,1-PAD-SQUARE
E$21, E$22, E$23: PASS-ROUND
E$25, E$26: 330k; 0207/12
E$27: 22k; 1206
E$28, E$29, E$62: SOD123
E$30: 1n; C1206K
E$31: 2nF; C1206K
E$32, E$33, E$38, E$64, E$77: HCPL181; TO-269AA
E$34, E$35: 1k; 1206
E$36, E$58: 1uF; C1206K
E$37: 8k2; 1206
E$39, E$55, E$56, E$59, E$65, E$69, E$78: 1k; 0805
E$40, E$47: 150p; C0805K
E$41: LMV6482; SO8
E$42, E$43, E$54, E$57, E$67: 4k7; 0805
E$44, E$60, E$63, E$66: 10k; 0805
E$45: 470; 0805
E$46: 680k; 0207/12
E$48, E$61: 22k; 0805
E$49: 270; 0805
E$50, E$68: Z5.1; MELF-MLL41
E$51, E$53: 10uF; C1206K
E$52: MA03-1
E$70: SML1206
E$71, E$82: 100k; 0207/12
E$72, E$83: LED5MM
E$79: 100; 1206
E$80: MA06-1
E$81: 47uF; EB20D
E$84: C102_152-062X184
E$85: L-160

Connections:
S$1: E$1.AC1, E$3.1, E$12.2, E$73.AC1
S$2: E$3.5, E$73.AC2
S$3: E$9.1, E$24.2
S$4: E$1.+, E$4.1, E$71.2
S$5: E$4.2, E$5.1, E$20.B4,1, E$25.1
S$6: E$2.AC2, E$3.9
S$7: E$2.AC1, E$3.7
S$8: E$65.2, E$80.5
S$9: E$2.+, E$6.+, E$10.IN
S$10: E$16.1, E$17.5, E$24.1, E$28.2, E$40.1
S$11: E$7.G, E$15.2
S$12: E$7.D, E$8.D, E$9.2, E$19.B4,1, E$46.2
S$13: E$8.G, E$14.2
S$14: E$11.3, E$11.4, E$11.7, E$14.1, E$15.1
S$15: E$11.6, E$11.8, E$44.1, E$45.2
S$16: E$10.OUT, E$11.1, E$11.2, E$13.+, E$17.8, E$18.8, E$41.8, E$42.1, E$49.2, E$58.1, E$60.1, E$77.-
S$17: E$25.2, E$26.2
S$18: E$27.1, E$28.1, E$30.2
S$19: E$17.6, E$26.1, E$30.1, E$34.1, E$40.2
S$20: E$33.-, E$34.2, E$37.1
S$21: E$17.1, E$18.1, E$32.-, E$42.2, E$45.1, E$47.1
S$22: E$41.6, E$59.1, E$60.2
S$23: E$18.2, E$43.1, E$46.1
S$24: E$17.2, E$29.2, E$31.1, E$48.1
S$25: E$18.3, E$29.1, E$35.1, E$48.2, E$49.1, E$50.1, E$51.2, E$64.-
S$26: E$17.3, E$53.2, E$54.2, E$68.1
S$27: E$32.AC1, E$33.AC1, E$38.+, E$64.AC1, E$67.1, E$77.AC1, E$80.1
S$28: E$33.AC2, E$55.2
S$29: E$32.AC2, E$56.2
S$30: E$55.1, E$80.3
S$31: E$17.7, E$31.2, E$35.2, E$52.3, E$63.1
S$32: E$52.2, E$54.1, E$64.+, E$66.1, E$67.2
S$33: E$56.1, E$80.2
S$34: E$38.-, E$80.4
S$36: E$38.AC2, E$39.2
S$37: E$39.1, E$41.7, E$69.1
S$38: E$1.-, E$2.-, E$5.2, E$6.-, E$7.S, E$8.S, E$10.GND, E$11.5, E$13.-, E$16.2, E$17.4, E$18.4, E$27.2, E$32.+, E$33.+, E$36.2, E$37.2, E$38.AC1, E$41.4, E$43.2, E$44.2, E$47.2, E$50.2, E$51.1, E$52.1, E$53.1, E$57.1, E$58.2, E$59.2, E$61.2, E$66.2, E$68.2, E$70.C, E$72.K, E$73.-, E$74.1, E$75.S, E$81.-, E$83.K
S$39: E$36.1, E$41.5, E$61.1, E$62.1
S$40: E$62.2, E$63.2
S$41: E$64.AC2, E$65.1
S$47: E$69.2, E$70.A
S$48: E$71.1, E$72.A
S$52: E$73.+, E$74.2, E$81.+, E$82.2, E$85.1
S$53: E$77.+, E$79.1
S$54: E$57.2, E$75.G, E$79.2
S$55: E$1.AC2, E$12.1
S$56: E$77.AC2, E$78.2
S$57: E$78.1, E$80.6
S$58: E$82.1, E$83.A
S$60: E$75.D, E$76.2, E$84.2, E$84.3
S$61: E$76.1, E$84.1, E$85.2

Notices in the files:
parts and their libraries:
raspberry_mirr: This library stands under the CERN Open Hardware Licence.
